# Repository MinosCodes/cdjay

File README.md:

# CDjay

## Introduction
The success of Pioneer's CDJ-Players is based on their usability and performance-oriented controls. And while the technology has evolved from CDs over SD-Cards to USB-Keys or direct interaction with a laptop, the control interface itself hasn't changed much. 
Modern CDJs, such as the CDJ-850, CDJ-900, CDJ-2000, and newer offer the possibility to directly connect to a host software, such as Algoriddim DJay, Native Instruments' Traktor, Serato Scratch, in order to be used as controller. 
The goal of this project is to bring this capability to older CDJ-Models in order to keep their control interface. 

## Related Work
A number of other projects have looked at the same idea. Some turning the CDJ into a MIDI-based controller, others integrating a RaspberryPi and running Mixxx, and open source DJ-Software on it, essentially turning them into full-blown, standalone, media-players. 

## Hardware
The goal is to provide drop-in replacement mainboards that communicate with the original hardware and bridge to a USB connection. All boards start from a Raspberry Pi Pico 2, but depending on the model, more or less additional hardware is required. See the individual files in the docs folder. 

## Interface
Since we want to focus on interfacing the old CDJs with the modern world (USB-C, Software, etc.), we use iPad mini running Algoriddim's djay in single deck mode, which gives us all the benefits such as touch interaction, integration to streaming services, etc.. Any iPad being able to run djay is fine, although interfacing is easier with the usb-c models. 

### Installation
Install djay from the App-Store on your iPad. Technically, it is possible to run djay from an iPhone, however, it doesn't support single-deck mode on smaller devices. 

### Connecting
If you have an iPad with a lightning-connector, you need a lightning to usb-converter that supports USB OTG. This will make the iPad the host of your USB connection, and the CDJay the client. 
For the USB-Models, just connect the USB-C connection to your iPad. 

## Acknowledgements

This project was supported by...

## Repositories
This work is part of a University project with its main focus is on teaching. 
The repository under https://git.fh-aachen.de/applab/projects/cdjay is the internal repo. 
The repository under https://github.com/applab-fhaachen/cdjay is a mirror to facilitate development with a larger community.

## Authors: 
Original contributors are 
- Florian H.
- Julius P.
- Konstantin P.
- Mike B.
- Nuno C.

## License
MIT License

All trademarks are property of their respective owners. This project is part of the education at FH Aachen University of Applied Sciences and not affiliated to any of the brand names.

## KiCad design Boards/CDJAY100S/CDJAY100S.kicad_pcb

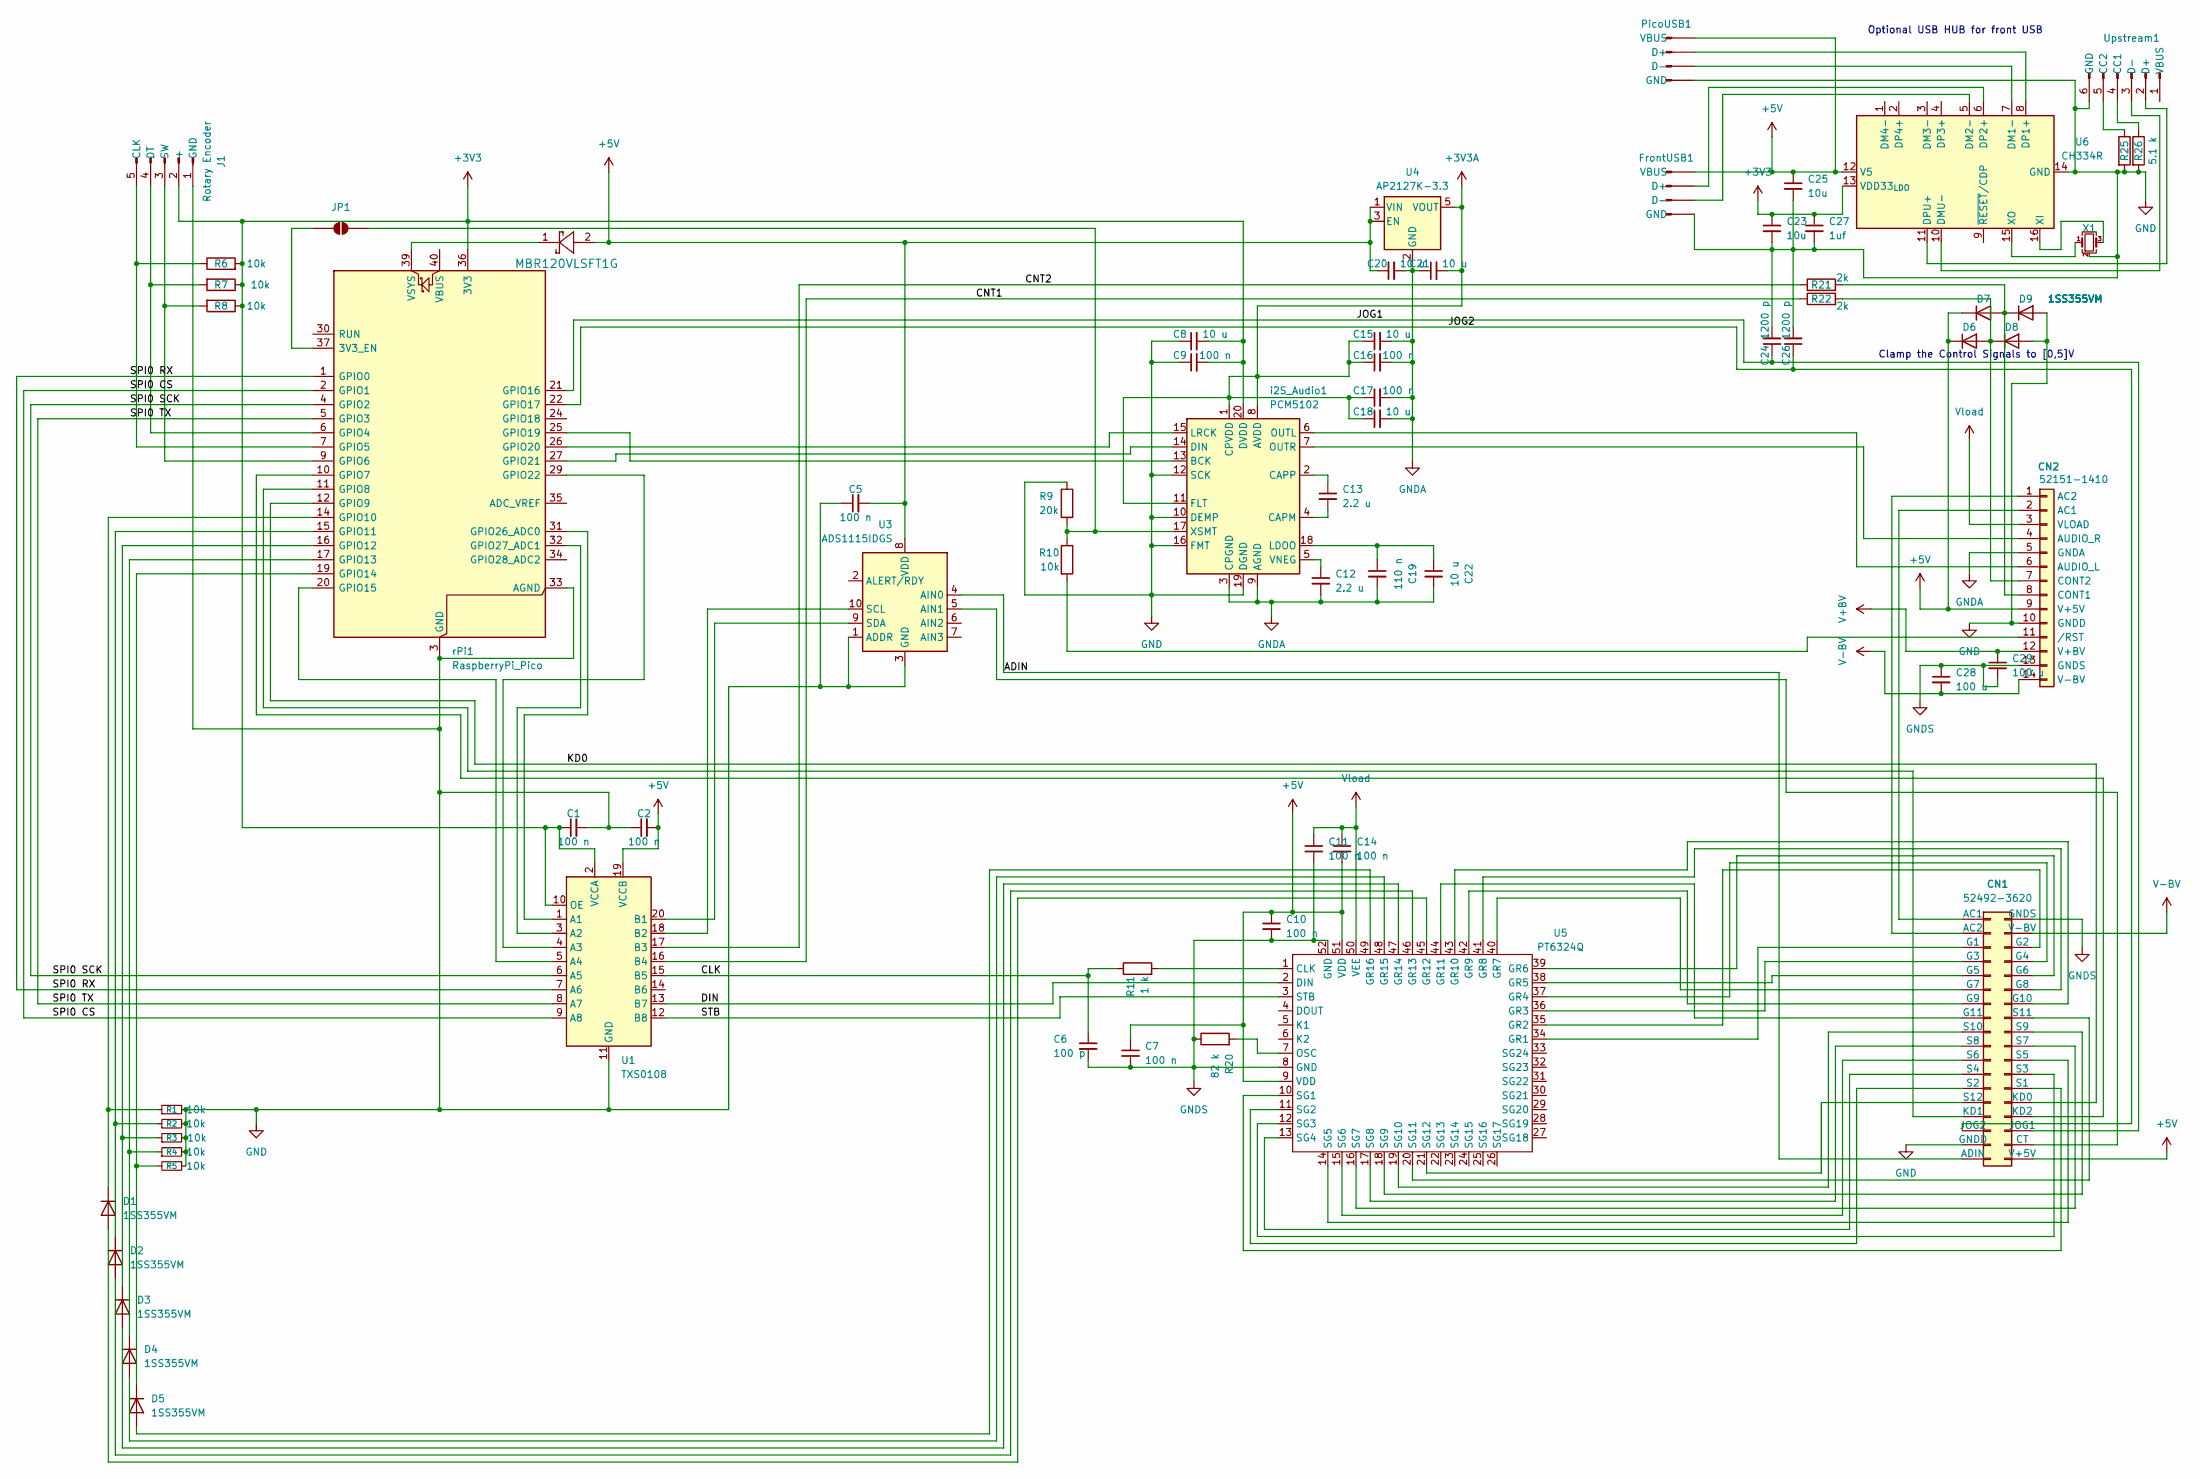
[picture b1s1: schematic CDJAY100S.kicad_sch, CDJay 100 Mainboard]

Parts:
C1, C2, C5, C7, C9, C10, C11, C14, C16, C17: 100 n; C_1206_3216Metric_Pad1.33x1.80mm_HandSolder
C6: 100 p; C_1206_3216Metric_Pad1.33x1.80mm_HandSolder
C8, C15, C18, C20, C21, C22: 10 u; C_1206_3216Metric_Pad1.33x1.80mm_HandSolder
C12, C13: 2.2 u; C_1206_3216Metric_Pad1.33x1.80mm_HandSolder
C19: 110 n; C_1206_3216Metric_Pad1.33x1.80mm_HandSolder
C23, C25: 10u; C_1206_3216Metric_Pad1.33x1.80mm_HandSolder
C24, C26: 1200 p; C_1206_3216Metric_Pad1.33x1.80mm_HandSolder
C27: 1uf; C_1206_3216Metric_Pad1.33x1.80mm_HandSolder
C28, C29: 100 u; C_1206_3216Metric_Pad1.33x1.80mm_HandSolder
CN1: 52492-3620; ConnectorFPC&FFC_MOL52045-3645-36P_1
CN2: 52151-1410; PinHeader_1x14_P2.00mm_Vertical
CNT1: MBR120VLSFT1G; Nexperia_CFP3_SOD-123W
D1, D2, D3, D4, D5, D6, D7, D8, D9: 1SS355VM; Nexperia_CFP3_SOD-123W
FrontUSB1: Conn_01x04_Pin; PinHeader_1x04_P2.54mm_Vertical
J1: Rotary Encoder; PinHeader_1x05_P2.54mm_Vertical
JP1: SolderJumper_2_Open; SolderJumper-2_P1.3mm_Open_Pad1.0x1.5mm
PicoUSB1: Conn_01x04_Pin; PinHeader_1x04_P2.54mm_Vertical
R1, R2, R3, R4, R5, R6, R7, R8, R10: 10k; R_1206_3216Metric_Pad1.30x1.75mm_HandSolder
R9: 20k; R_1206_3216Metric_Pad1.30x1.75mm_HandSolder
R11: 1 k; R_1206_3216Metric_Pad1.30x1.75mm_HandSolder
R20: 82 k; R_1206_3216Metric_Pad1.30x1.75mm_HandSolder
R21, R22: 2k; R_1206_3216Metric_Pad1.30x1.75mm_HandSolder
R25, R26: 5.1 k; R_1206_3216Metric_Pad1.30x1.75mm_HandSolder
U1: TXS0108; TSSOP-20_4.4x6.5mm_P0.65mm
U3: ADS1115IDGS; TSSOP-10_3x3mm_P0.5mm
U4: AP2127K-3.3; SOT-23-5
U5: PT6324Q; QFP-52_14x14mm_P1mm_1
U6: CH334R; QSOP-16_3.9x4.9mm_P0.635mm
Upstream1: Conn_01x06_Pin; PinHeader_1x06_P2.54mm_Vertical
X1: 12MHz; Crystal_SMD_3225-4Pin_3.2x2.5mm_HandSoldering
i2S_Audio1: PCM5102; TSSOP-20_4.4x6.5mm_P0.65mm; PARTREV C
rPi1: RaspberryPi_Pico; RaspberryPi_Pico_Common_Unspecified

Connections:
+3V3: C1.1, C8.2, C9.2, C23.1, C27.1, J1.2 (+), R6.2, R7.1, R8.1, U1.2 (VCCA), U1.10 (OE), U6.13 (VDD33_{LDO}), i2S_Audio1.20 (DVDD), rPi1.36 (3V3)
+3V3A: C15.1, C16.1, C17.1, C18.1, C21.2, U4.5 (VOUT), i2S_Audio1.1 (CPVDD), i2S_Audio1.8 (AVDD), i2S_Audio1.11 (FLT)
+5V: C2.2, C5.2, C7.1, C10.1, C14.2, C20.1, C25.1, CN1.1 (V+5V), CN2.9 (V+5V), CNT1.2, D6.1 (K), D7.1 (K), FrontUSB1.1 (VBUS), PicoUSB1.1 (VBUS), U1.19 (VCCB), U3.8 (VDD), U4.1 (VIN), U4.3 (EN), U5.9 (VDD), U5.51 (VDD), U6.12 (V5)
/ADIN: CN1.2 (ADIN), U3.4 (AIN0)
/CLK: C6.1, R11.1, U1.15 (B5)
/CNT1: R22.1, U1.16 (B4)
/CNT2: R21.1, U1.17 (B3)
/DIN: U1.13 (B7), U5.2 (DIN)
/JOG1: C24.1, CN1.5 (JOG1), rPi1.21 (GPIO16)
/KD0: CN1.9 (KD0), rPi1.12 (GPIO9)
/SPI0 CS: U1.9 (A8), rPi1.2 (GPIO1)
/SPI0 RX: U1.7 (A6), rPi1.1 (GPIO0)
/SPI0 SCK: U1.6 (A5), rPi1.4 (GPIO2)
/SPI0 TX: U1.8 (A7), rPi1.5 (GPIO3)
/STB: U1.12 (B8), U5.3 (STB)
GNDA: C12.2, C15.2, C16.2, C17.2, C18.2, C19.2, C20.2, C21.1, C22.2, CN2.5 (GNDA), U4.2 (GND), i2S_Audio1.3 (CPGND), i2S_Audio1.9 (AGND)
GNDS: C6.2, C7.2, C10.2, C11.2, C28.1, C29.2, CN1.35 (GNDS), CN2.13 (GNDS), R20.1, U5.8 (GND), U5.52 (GND)
unnamed: CN1.36 (AC1), CN2.2 (AC1)
unnamed: CN1.34 (AC2), CN2.1 (AC2)
unnamed: CN1.3 (CT), U3.5 (AIN1)
unnamed: CN1.32 (G1), U5.34 (GR1)
unnamed: CN1.31 (G2), U5.35 (GR2)
unnamed: CN1.30 (G3), U5.36 (GR3)
unnamed: CN1.29 (G4), U5.37 (GR4)
unnamed: CN1.28 (G5), U5.38 (GR5)
unnamed: CN1.27 (G6), U5.39 (GR6)
unnamed: CN1.26 (G7), U5.40 (GR7)
unnamed: CN1.25 (G8), U5.41 (GR8)
unnamed: CN1.24 (G9), U5.42 (GR9)
unnamed: CN1.23 (G10), U5.43 (GR10)
unnamed: CN1.22 (G11), U5.44 (GR11)
unnamed: CN1.8 (KD1), rPi1.11 (GPIO8)
unnamed: CN1.7 (KD2), rPi1.10 (GPIO7)
unnamed: CN1.11 (S1), U5.10 (SG1)
unnamed: CN1.12 (S2), U5.11 (SG2)
unnamed: CN1.13 (S3), U5.12 (SG3)
unnamed: CN1.14 (S4), U5.13 (SG4)
unnamed: CN1.15 (S5), U5.14 (SG5)
unnamed: CN1.16 (S6), U5.15 (SG6)
unnamed: CN1.17 (S7), U5.16 (SG7)
unnamed: CN1.18 (S8), U5.17 (SG8)
unnamed: CN1.19 (S9), U5.18 (SG9)
unnamed: CN1.20 (S10), U5.19 (SG10)
unnamed: CN1.21 (S11), U5.20 (SG11)
unnamed: CN1.10 (S12), U5.21 (SG12)
unnamed: CN2.6 (AUDIO_L), i2S_Audio1.6 (OUTL)
unnamed: CN2.4 (AUDIO_R), i2S_Audio1.7 (OUTR)
unnamed: CN2.8 (CONT1), D7.2 (A), D9.1 (K), R21.2
unnamed: CN2.7 (CONT2), D6.2 (A), D8.1 (K), R22.2
unnamed: CN2.11 (/RST), R10.2
unnamed: D1.2 (A), U5.45 (GR12)
unnamed: D1.1 (K), R1.1, rPi1.14 (GPIO10)
unnamed: D2.2 (A), U5.46 (GR13)
unnamed: D2.1 (K), R2.1, rPi1.15 (GPIO11)
unnamed: D3.2 (A), U5.47 (GR14)
unnamed: D3.1 (K), R3.1, rPi1.16 (GPIO12)
unnamed: D4.2 (A), U5.48 (GR15)
unnamed: D4.1 (K), R4.1, rPi1.17 (GPIO13)
unnamed: D5.2 (A), U5.49 (GR16)
unnamed: D5.1 (K), R5.2, rPi1.19 (GPIO14)
unnamed: FrontUSB1.2 (D+), U6.6 (DP2+)
unnamed: FrontUSB1.3 (D-), U6.5 (DM2-)
unnamed: J1.5 (CLK), R6.1, rPi1.7 (GPIO5)
unnamed: J1.4 (DT), R7.2, rPi1.6 (GPIO4)
unnamed: J1.3 (SW), R8.2, rPi1.9 (GPIO6)
unnamed: JP1.1 (A), rPi1.37 (3V3_EN)
unnamed: JP1.2 (B), R9.2, R10.1, i2S_Audio1.17 (XSMT)
unnamed: PicoUSB1.2 (D+), U6.8 (DP1+)
unnamed: PicoUSB1.3 (D-), U6.7 (DM1-)
unnamed: U1.1 (A1), rPi1.31 (GPIO26_ADC0)
unnamed: U1.3 (A2), rPi1.32 (GPIO27_ADC1)
unnamed: U1.4 (A3), rPi1.29 (GPIO22)
unnamed: U1.5 (A4), rPi1.20 (GPIO15)
unnamed: U1.20 (B1), U3.9 (SDA)
unnamed: U1.18 (B2), U3.10 (SCL)
unnamed: R11.2, U5.1 (CLK)
unnamed: R20.2, U5.7 (OSC)
unnamed: U6.10 (DMU-), Upstream1.3 (D-)
unnamed: U6.11 (DPU+), Upstream1.2 (D+)
unnamed: U6.16 (XI), X1.3
unnamed: U6.15 (XO), X1.1
unnamed: R26.1, Upstream1.4 (CC1)
unnamed: R25.1, Upstream1.5 (CC2)
unnamed: i2S_Audio1.13 (BCK), rPi1.25 (GPIO19)
unnamed: C13.2, i2S_Audio1.4 (CAPM)
unnamed: C13.1, i2S_Audio1.2 (CAPP)
unnamed: i2S_Audio1.14 (DIN), rPi1.27 (GPIO21)
unnamed: C19.1, C22.1, i2S_Audio1.18 (LDOO)
unnamed: i2S_Audio1.15 (LRCK), rPi1.26 (GPIO20)
unnamed: C12.1, i2S_Audio1.5 (VNEG)
unnamed: CNT1.1, rPi1.39 (VSYS)
V+BV: C29.1, CN2.12 (V+BV)
V-BV: C28.2, CN1.33 (V-BV), CN2.14 (V-BV)
Vload: C11.1, C14.1, CN2.3 (VLOAD), U5.50 (VEE)

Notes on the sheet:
Clamp the Control Signals to [0,5]V
Optional USB HUB for front USB

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
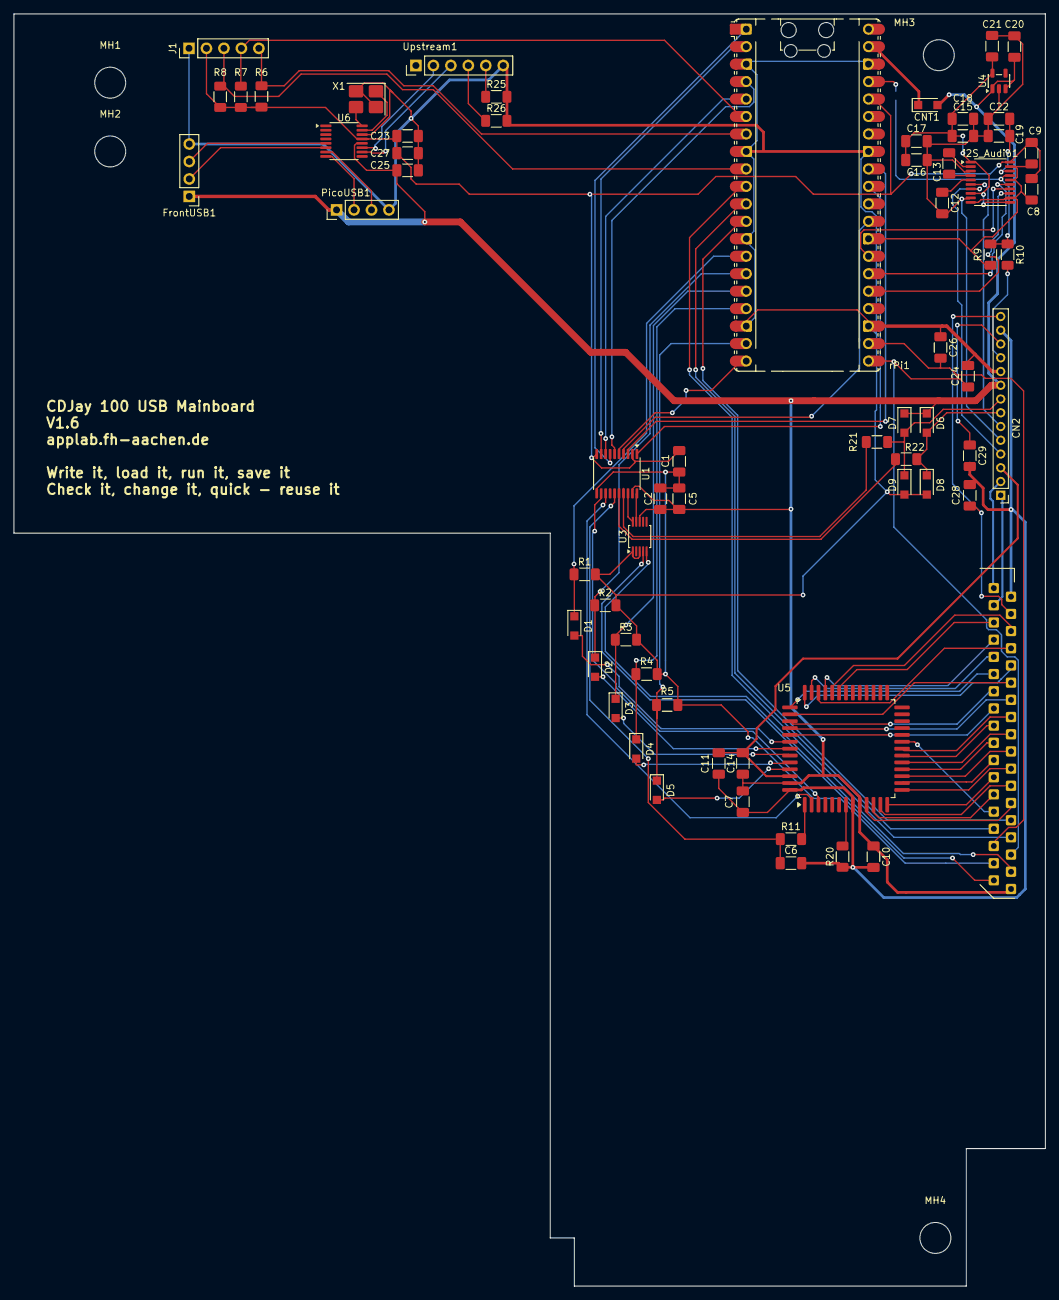
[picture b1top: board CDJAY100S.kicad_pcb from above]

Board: 2 copper layers, 150.0 x 185.0 mm, 72 parts (1 on the bottom side), 96 nets.

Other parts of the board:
MH1, MH2, MH3, MH4: MountingHole_4.5mm

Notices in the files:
Boards/CDJAY100S/CDJAY100S.kicad_pcb:
CC-By-SA
